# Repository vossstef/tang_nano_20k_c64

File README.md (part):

# C64Nano

The C64Nano is a port of some [MiST](https://github.com/mist-devel/mist-board/wiki) and
[MiSTer](https://mister-devel.github.io/MkDocs_MiSTer/) core components for the
[C64](https://en.wikipedia.org/wiki/Commodore_64):

| Board      | FPGA       | support |Note|
| ---        |        -   | -     |-|
| [Tang Nano 20k](https://wiki.sipeed.com/nano20k)     | [GW2AR](https://www.gowinsemi.com/en/product/detail/38/)  | HDMI / LCD |Dualshock via MiSTeryShield20k spare header **or** Joy to DIP |
| [Tang Primer 25K](https://wiki.sipeed.com/hardware/en/tang/tang-primer-25k/primer-25k.html) | [GW5A-25](https://www.gowinsemi.com/en/product/detail/60/) | HDMI |no Dualshock, no Retro D9 Joystick, no MIDI |
| [Tang Mega 60k NEO](https://wiki.sipeed.com/hardware/en/tang/tang-mega-60k/mega-60k.html) | [GW5AT-60](https://www.gowinsemi.com/en/product/detail/60/) | HDMI / LCD | twin Dualshock |
| [Tang Mega 138k Pro](https://wiki.sipeed.com/hardware/en/tang/tang-mega-138k/mega-138k-pro.html)|[GW5AST-138](https://www.gowinsemi.com/en/product/detail/60/) | HDMI / LCD |twin Dualshock |
| [Tang Console 60K NEO](https://wiki.sipeed.com/hardware/en/tang/tang-console/mega-console.html)|[GW5AT-60](https://www.gowinsemi.com/en/product/detail/60/) | HDMI / LCD |twin Dualshock, no Retro D9 Joystick|

Be aware that the [VIC20](https://en.wikipedia.org/wiki/VIC-20) ([VIC20Nano](https://github.com/vossstef/VIC20Nano)),
[Atari 2600 VCS](https://en.wikipedia.org/wiki/Atari_2600) ([A2600Nano](https://github.com/vossstef/A2600Nano)), [Apple IIe](https://en.wikipedia.org/wiki/Apple_IIe) ([NanoApple2](https://github.com/vossstef/NanoApple2)) had been ported too in similar manner.  

This project relies on an external µC being connected to the Tang Nano 20K. You can use a [M0S Dock BL616](https://wiki.sipeed.com/hardware/en/maixzero/m0s/m0s.html), [Raspberry Pi Pico (W)](https://www.raspberrypi.com/documentation/microcontrollers/pico-series.html) or [esp32-s2](https://www.espressif.com/en/products/socs/esp32-s2)/[s3](https://www.espressif.com/en/products/socs/esp32-s3) and use the [FPGA companion firmware](http://github.com/harbaum/FPGA-Companion). Basically a µC acts as USB host for USB devices and as an OSD controller using a [SPI communication protocol](https://github.com/harbaum/MiSTeryNano/blob/main/SPI.md).

Onboard BL616 µC  
* If you don't need the WIFI modem on a TN20K then even the onboard BL616 µC (normally used for bitstream programming) can be used. A dedicated FPGA bitstream and FPGA companion firmware is needed in that configuration. The onboard BL616 µC is presently supported for TN20K and Console 60K boards. WIFI modem is supported on Console 60K too. There is an extern powered (see ->) [USB Hub](https://github.com/harbaum/FPGA-Companion/blob/main/console_usbhub_and_power_over_usb-a.png) + USB-A to USB-A cable + USB-A Power Supply Plug needed to supply the board and at the same time provide USB ports for USB Keyboard and e.g. USB Joystick or Mouse.

For the [M0S Dock](https://wiki.sipeed.com/hardware/en/maixzero/m0s/m0s.html) BL616 [µC](https://en.bouffalolab.com) there is a:

* [Optional custom carrier board MiSTeryShield20k](https://github.com/harbaum/MiSTeryNano/tree/main/board/misteryshield20k/README.md)
* [M0S PMOD Adapter](https://github.com/harbaum/MiSTeryNano/blob/main/board/m0s_pmod) for Primer / Mega / Console Boards
* [Optional case](https://github.com/harbaum/MiSTeryNano/blob/main/board/misteryshield20k/housing3D)
* [Dualshock Adapter / Cable](/board/misteryshield20k_ds2_adapter/misteryshield20k_ds2_adapter_cable.md)

and for the Raspberry PiPico (RP2040 µC) there is a:

* [Optional custom carrier board MiSTeryShield20k Raspberry PiPico](/board/misteryshield20k_rpipico/README.md)
* [Dualshock Adapter / Cable](/board/misteryshield20k_ds2_adapter/misteryshield20k_ds2_adapter_cable.md)
* [Optional custom PMOD RP2040-Zero](/board/pizero_pmod/README.md) for Primer / Mega / Console Boards
* [Optional custom PMOD PiPico W](/board/pipico_pmod/README.md) incl. WIFI-modem for Primer / Mega / Console Boards
  
Original C64 core by Peter Wendrich and c1541 by [darfpga](https://github.com/darfpga).  
All HID components and µC firmware by Till Harbaum

Features:

* PAL 800x576p@50Hz or NTSC 800x480p@60Hz HDMI Video and Audio Output
* TFT-LCD module 800x600 [SH500Q01Z](https://dl.sipeed.com/Accessories/LCD/500Q01Z-00%20spec.pdf) + Speaker support
* USB Keyboard
* [USB Joystick](https://en.wikipedia.org/wiki/Joystick) or [USB Gamepad](https://en.wikipedia.org/wiki/Gamepad)
* [USB Mouse](https://en.wikipedia.org/wiki/Computer_mouse) as [c1351](https://en.wikipedia.org/wiki/Commodore_1351) Mouse emulation
* [USB Gamepad](https://en.wikipedia.org/wiki/Gamepad) Stick as [Paddle](https://www.c64-wiki.com/wiki/Paddle) Emulation
* [USB XBOX 360 Controller](https://en.wikipedia.org/wiki/Xbox_360_controller) as Joystick or Paddle
* [legacy D9 Joystick](https://en.wikipedia.org/wiki/Atari_CX40_joystick) (Atari / Commodore digital type)
* Joystick emulation on Keyboard Numpad
* [Dualshock 2 Controller Gamepad](https://en.wikipedia.org/wiki/DualShock) for [MiSTeryShield20k](https://github.com/harbaum/MiSTeryNano/tree/main/board/misteryshield20k/README.md) via spare [pinheader](/board/misteryshield20k_ds2_adapter/misteryshield20k_ds2_adapter_cable.md). Adapter [venice1200](https://github.com/venice1200)
* [Dualshock 2 Gamepad](https://en.wikipedia.org/wiki/DualShock) DPad / left Stick as Joystick
* [Dualshock 2 Gamepad](https://en.wikipedia.org/wiki/DualShock) Sticks as [Paddle](https://www.c64-wiki.com/wiki/Paddle) Emulation (analog mode)
* Emulation of [C64GS Cheetah Annihilator](https://en.wikipedia.org/wiki/Commodore_64_Games_System) Joystick 2nd Trigger Button (Pot X/Y)
* emulated [1541 Diskdrive](https://en.wikipedia.org/wiki/Commodore_1541) on FAT/extFAT microSD card with parallel bus [Speedloader Dolphin DOS 2](https://rr.pokefinder.org/wiki/Dolphin_DOS). [GER manual](https://www.c64-wiki.de/wiki/Dolphin_DOS)
* c1541 DOS ROM selection
* Cartridge ROM (*.CRT) loader
* Direct BASIC program (*.PRG) injection loader
* Tape (*.TAP) image loader as [C1530 Datasette](https://en.wikipedia.org/wiki/Commodore_Datasette)
* Loadable 8K Kernal ROM (*.BIN)
* [VIC-II](https://en.wikipedia.org/wiki/MOS_Technology_VIC-II) revision and [6526](https://en.wikipedia.org/wiki/MOS_Technology_CIA) / 8521 selection
* [SID](https://en.wikipedia.org/wiki/MOS_Technology_6581) revision 6581 or 8580 selectable
* 2nd dual SID Option and loadable Filter curves
* emulated [RAM Expansion Unit (REU)](https://en.wikipedia.org/wiki/Commodore_REU) or [GeoRAM](https://en.wikipedia.org/wiki/GeoRAM)
* On Screen Display (OSD) for configuration and loadable image selection (D64/G64/CRT/PRG/BIN/TAP/FLT)
* Physical MIDI-IN and OUT
* RS232 Serial Interface [VIC-1011](http://www.zimmers.net/cbmpics/xother.html) or [UP9600](https://www.pagetable.com/?p=1656) mode to Tang onboard USB-C serial port or external hw pin.
* Swiftlink-232 [6551](https://en.wikipedia.org/wiki/MOS_Technology_6551) WIFI Modem Interface to FPGA-Companion up to 38400 Baud
* Freezer support (e.g. Action Replay)

## Installation

The installation of C64 Nano on the Tang Nano 20k board can be done using a Linux PC or a Windows PC
[(Instruction)](INSTALLATION_WINDOWS.md).

## c64 Nano on Tang Primer 25K

See [Tang Primer 25K](TANG_PRIMER_25K.md). PMOD TF-CARD V2 is required !

## c64 Nano on Tang Mega 60k NEO

See [Tang Mega 60K NEO](TANG_MEGA_60K.md)

## c64 Nano on Tang Mega 138k Pro

See [Tang Mega 138K Pro](TANG_MEGA_138Kpro.md)

## c64 Nano on Tang Console 60k NEO

See [Tang Console 60K NEO](TANG_CONSOLE_60K.md)

## c64 Nano with LCD and Speaker

See [Tang Nano LCD](TANG_NANO_20k_LCD.md)

## emulated Diskdrive c1541

Emulated 1541 on a regular FAT/exFAT formatted microSD card including parallel bus Speedloader Dolphin DOS 2.0.
Copy a D64 Disk image to your sdcard and rename it to **disk8.d64** as default boot image.
Add further D64 or G64 images as you like and insert card in TN slot. LED 0 acts as Drive activity indicator.

> [!TIP]
> Disk directory listing: [(or F7 keypress)](https://project64.c64.org/hw/dolphindos.txt)  
> command:  
> LOAD"$",8  
> LIST  
> Load first program from Disk: (or just LOAD if Dolphin Kernal active)  
> LOAD"*",8  
> RUN  

c1541 DOS ROM can be selected from OSD (default Dolphin DOS 2.0, CBM DOS, SpeedDos Plus or JiffyDOS)
In case a program don't load correctly select via OSD the factory default CBM DOS an give it a try.

## Cartridge ROM Loader (.CRT)

Cartridge ROM can be loaded via OSD file selection.
Copy a *.CRT to your sdcard and rename it to **c64crt.crt** as default boot cartridge ROM.
Prevent the cartridge load at boot by OSD CRT selection **No Disk** , **Save settings** and System **Cold Boot**.
> [!TIP]
> **Detach Cartridge** by OSD:
> ```temporary``` **Cartridge unload & Reset** ```permanent``` **No Disk**, **Save settings** and System **Cold Boot**

> [!IMPORTANT]
> Be aware that some Freezer Card CRT might require to use the standard C64 Kernal and the standard C1541 CBM DOS.

## BASIC Program Loader (.PRG)

A BASIC Program *.PRG file can be loaded via OSD file selection.
Copy a .PRG to your sdcard and rename it to **c64prg.prg** as default boot basic program. Prevent the PRG load at boot by OSD PRG selection **No Disk** , **Save settings** and **Reset** or System **Cold Boot**.
> [!TIP]
> Check loaded file by command: **LIST**

> [!IMPORTANT]
> command: **RUN**

## Tape Image Loader (*.TAP)

A [Tape](https://en.wikipedia.org/wiki/Commodore_Datasette) *.TAP file can be loaded via OSD file selection
In order to start a tape download choose C64 CBM Kernal (mandatory as Dolphin DOS doesn't support Tape). Best to save Kernal OSD selection via **Save settings**.
> [!IMPORTANT]
> command: **LOAD**  
> ___ Only if you have [Exbasic Level II](https://www.c64-wiki.de/index.php?title=Exbasic_Level_II&oldid=261004). CRT Basic loaded then use command: 
> **LOAD***  
> Screen will blank!

The file is loaded automatically as soon as TAP file selected via OSD (no need to press PLAY TAPE button) in case ***no** TAP had been previously selected*.
As mentioned screen will blank for several seconds and then display briefly the filename of the to be loaded file. It will blank shortly afterwards again till load completed and take a lot of time...
Copy a *.TAP to your sdcard and rename it to **c64tap.tap** as default tape mountpoint.
For **Tape unload** use OSD TAP selection **No Disk** and **Reset** or System **Cold Boot**
> [!WARNING]
> After board power-up or coldboot a TAP file will **not autoloaded** even if TAP file selection had been saved or c64tap.tap mountpoint available !
> Unblock loader by OSD TAP selection **No Disk** or simply select again the desired TAP file to be loaded after you typed **LOAD**

> [!TIP]
> Check loaded file by command: **LIST**

> [!IMPORTANT]
> command: **RUN**

> [!NOTE]
> The available (muffled) Tape Sound audio can be disabled from OSD.

## Kernal Loader (.BIN)

The build-in Dolphin Kernal is the power-up default C64 Kernal with an excellent C1541 speedloader.
> [!TIP]
> If you are fine with that then there is no need to load another Kernal via OSD and just select OSD Kernal BIN selection **No Disk** and **Save settings**!

In general Kernal ROM files *.BIN can be loaded via OSD selection.
Copy a 8K C64 Kernal ROM .BIN to your sdcard and rename it to **c64kernal.bin** as default boot Kernal.
Prevent Kernal load by OSD Kernal BIN selection **No Disk** and **Save settings** and do a **power-cyle** of the board. In this case the build-in Dolphin Kernal will by default be used after next power cycle.

## SID Filter Curve (.FLT)

Custom Filters curves can optionally be loaded via OSD.
> [!TIP]https://www.telnetbbsguide.com/bbs/software/image-bbs/
> This is in most cases not needed and build-in filters curves are already an optimum.

> [!NOTE]
> Remember to select the 6581 chip, not the 8580.
> Select 'Custom 1' as the filter to activate it. When a custom filter is loaded, there's no difference between custom options Custom 1, 2, and 3. Selecting 'Default' switches back to the built-in filter curve.
https://www.telnetbbsguide.com/bbs/software/image-bbs/
Prevent Filter curve load by OSD Kernal **FLT** selection **No Disk** and **Save settings** and **power-cyle** of the board.

## Core Loader Sequencing

The core will after power cycle/ cold-boot start downloading the images on the sdcard in the following order:

> [!NOTE]
> (1) BIN Kernal, (2) CRT ROM, (3) PRG Basic and finally (4) FLT.

## emulated RAM Expansion Unit REU 1750

For those programs the require a [RAM Expansion Unit (REU)](https://en.wikipedia.org/wiki/Commodore_REU) it can be activated by OSD on demand.

Playing [Sonic the Hedgehog V1.2](https://csdb.dk/release/?id=212523)
Enable REU, and load the PRG.  
Playing around with [GEOS](https://en.wikipedia.org/wiki/GEOS_(8-bit_operating_system))
Enable REU, select c1541 CBM DOS ROM and load the PRG.

## Push Button / DIP Switch utilization

* S1 swap the Joystick Ports if OSD **Swap Joys** is set to Off mode.

* S2 open OSD

> [!CAUTION]
> A FLASH programm attempt without keeping the board in reset may lead to corruption of the C1541 DOS images stored in FLASH requiring re-programming.
> Nano 20k S2 keep pressed during power-up for FLASH programming of FPGA bitstream  

## OSD

invoke by F12 keypress

* Reset
* Cold Reset + memory scrubbing
* Audio Volume + / -
* Scanlines effect %
* Widescreen activation
* HID device selection for Joystick Port 1 and Port 2
* REU activation
* c1541 Drive disk image selection
* c1541 Disk write protetcion
* c1541 Reset
* c1541 DOS ROM selection
* MIDI configuration
* PAL / NTSC Video mode
* VIC-II revision, 6526 / 8521 and SID 6561/8580 selection
* SID Filter selection
* geoRAM activation
* Loader (CRT/PRG/BIN/TAP/FLT) file selection
* Joystick Port Swap
* Cartridge unload

## Gamecontrol support

<u>legacy single D9 Digital Joystick.</u>  
OSD: **Retro D9**
Atari ST type of Joystick 2nd button supported using a MiSTeryNano shield.  
Don't configure e.g. [ArcadeR](https://retroradionics.com) for C64 mode rather than normal digital 2nd button mode (2nd trigger button connect signal to ground)

<u>USB Joystick(s)</u>.  
OSD: **USB #1 Joy** or **USB #2 Joy**
Also [RII Mini Keyboard i8](http://www.riitek.com/product/220.html) left Multimedia Keys are active if **USB #1 Joy** selected.

<u>Dualshock 2 Gamepad Stick or Dpad as Joystick.</u>.  
OSD: **DS #1 Joy** or **DS #2 Joy**
At the moment Dpad only for original Pad. Some clone devices support at the same time Dpad and left stick simultaniously. ```circle and cross``` Buttons as Trigger:

> [!IMPORTANT]
> In a [MiSTeryShield20k](https://github.com/harbaum/MiSTeryNano/tree/main/board/misteryshield20k) configuration Dualshock is supported via the internal ``spare J8`` pinheader.
> See [MiSTeryShield20k DS2 Adapter / Cable](/board/misteryshield20k_ds2_adapter/misteryshield20k_ds2_adapter_cable.md) for further information. Thx [venice1200](https://github.com/venice1200) !

> [!NOTE]
> TN20k: You have to select OSD **DS2 #2 Joy** or **DS #2 Paddle** for a ``MiSTeryShield20k`` configuration.
> TN20k: You have to select OSD **DS2 #1 Joy** or **DS #1 Paddle** if you use the ``Sipeed Joy to DIP`` adapter.
> Single DS interface active at the same time!

<u>Keyboard Numpad.</u>  
OSD: **Numpad**

|Numpad| |Numpad|
|-|-|-|
|0  Trigger|8  Up|.  Trigger 2|
|4  Left|-|6  Right|
|-|2  Down|-|

<u>Mouse.</u>  
OSD: **Mouse**
USB Mouse as c1351 Mouse emulation.

<u>Dualshock 2 Gamepad</u> as Paddle  
OSD: **DS #1 Paddle** or **DS #2 Paddle**
Dualshock left Stick in analog mode as VC-1312 Paddle emulation.
ANALOG Paddle mode will be indicated by DS 2 red light indicator.
> [!NOTE]
> TN20k:
> single Dualshock support only
> 4 Paddles mapped to a single Gamepad (X/Y) and both Sticks.
> **square** , **cross**, **circle** and **triangle** used as 4 Trigger buttons
> ``Joyport 1:``  **DS2 #1 Paddle**
> ``Joyport 2:``  **DS2 #1 Paddle**
> or<br>
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
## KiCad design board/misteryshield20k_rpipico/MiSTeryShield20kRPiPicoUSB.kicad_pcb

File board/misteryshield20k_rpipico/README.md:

# MiSTeryShield20k RPiPico USB board

Features:

* Headers to plug the Tang Nano 20K
* Headers to plug the [Raspberry Pi Pico (W)](https://www.raspberrypi.com/products/raspberry-pi-pico)
* Atari / Commodore style joystick interface
  * Supports up to two buttons
  * Including 5V supply and 5V level shifters
  * Works with DB9 joystcks and mice
  * MIDI
    * MIDI OUT with driver chip to protect Tang Nano 20K
    * MIDI IN with optocoupler to protect Tang Nano 20K
* 4 x USB-A Interface
* Spare header for FPGA IO / [Dualshock 2 Adapter cable](/board/misteryshield20k_ds2_adapter/misteryshield20k_ds2_adapter_cable.md) (**no DS2 connector onboard**)
* Debug header for Pico UART and e.g. FPGA UART
* 3 x PiPico Status LED
* 3D STEP model to ease case development
* [CERN-OHL-S](https://cern-ohl.web.cern.ch/home) license

PCBA production files for [JLCPCB](https://jlcpcb.com) are availble [here](Output/production)  
(Fully assembled boards can orderd based on BOM partlist, excluding the TN20k and PiPico connector)  

The great PCB Layout work using [KiCad](https://www.kicad.org) had been done by [cantclosevi](https://github.com/cantclosevi). Thx Michal !

**Version history**
| Version  | Issue|  Change to earlier version|rework|
|----------|-|--------|-|
|0|engineering sample|DS2 connector rotated|mount DS2 bottom|
|1|DS2 rotation fixed|mechanical positioning|-|
|2|DS2 removed and positioning fixed|MIDI IN pin 4+5 reversed|[Instruction](rework/REWORK_HW2.MD)|
|3| none known |MIDI IN fix|-|

# Pin usage

| Pin  | Signal | Description            |
|------|--------|------------------------|
| GP0  | UART_TX| Serial debug output    |
| GP1  | UART_RX| Serial debug input     |
| GP2  | USB D+ | USB PIO host D+        |
| GP3  | USB D- | USB PIO host D-        |
| GP4  | LED 1  | indicator mice         |
| GP5  | LED 2  | indicator keyboard     |
| GP6  | LED 3  | indicator joystick     |
| GP16 | MISO   | SPI data from FPGA     |
| GP17 | CSn    | SPI chip select to FPGA|
| GP18 | SCK    | SPI clock to FPGA      |
| GP19 | MOSI   | SPI data to FPGA       |
| GP20 |spare   | spare                  |
| GP22 | IRQn   | SPI interrupt from FPGA|

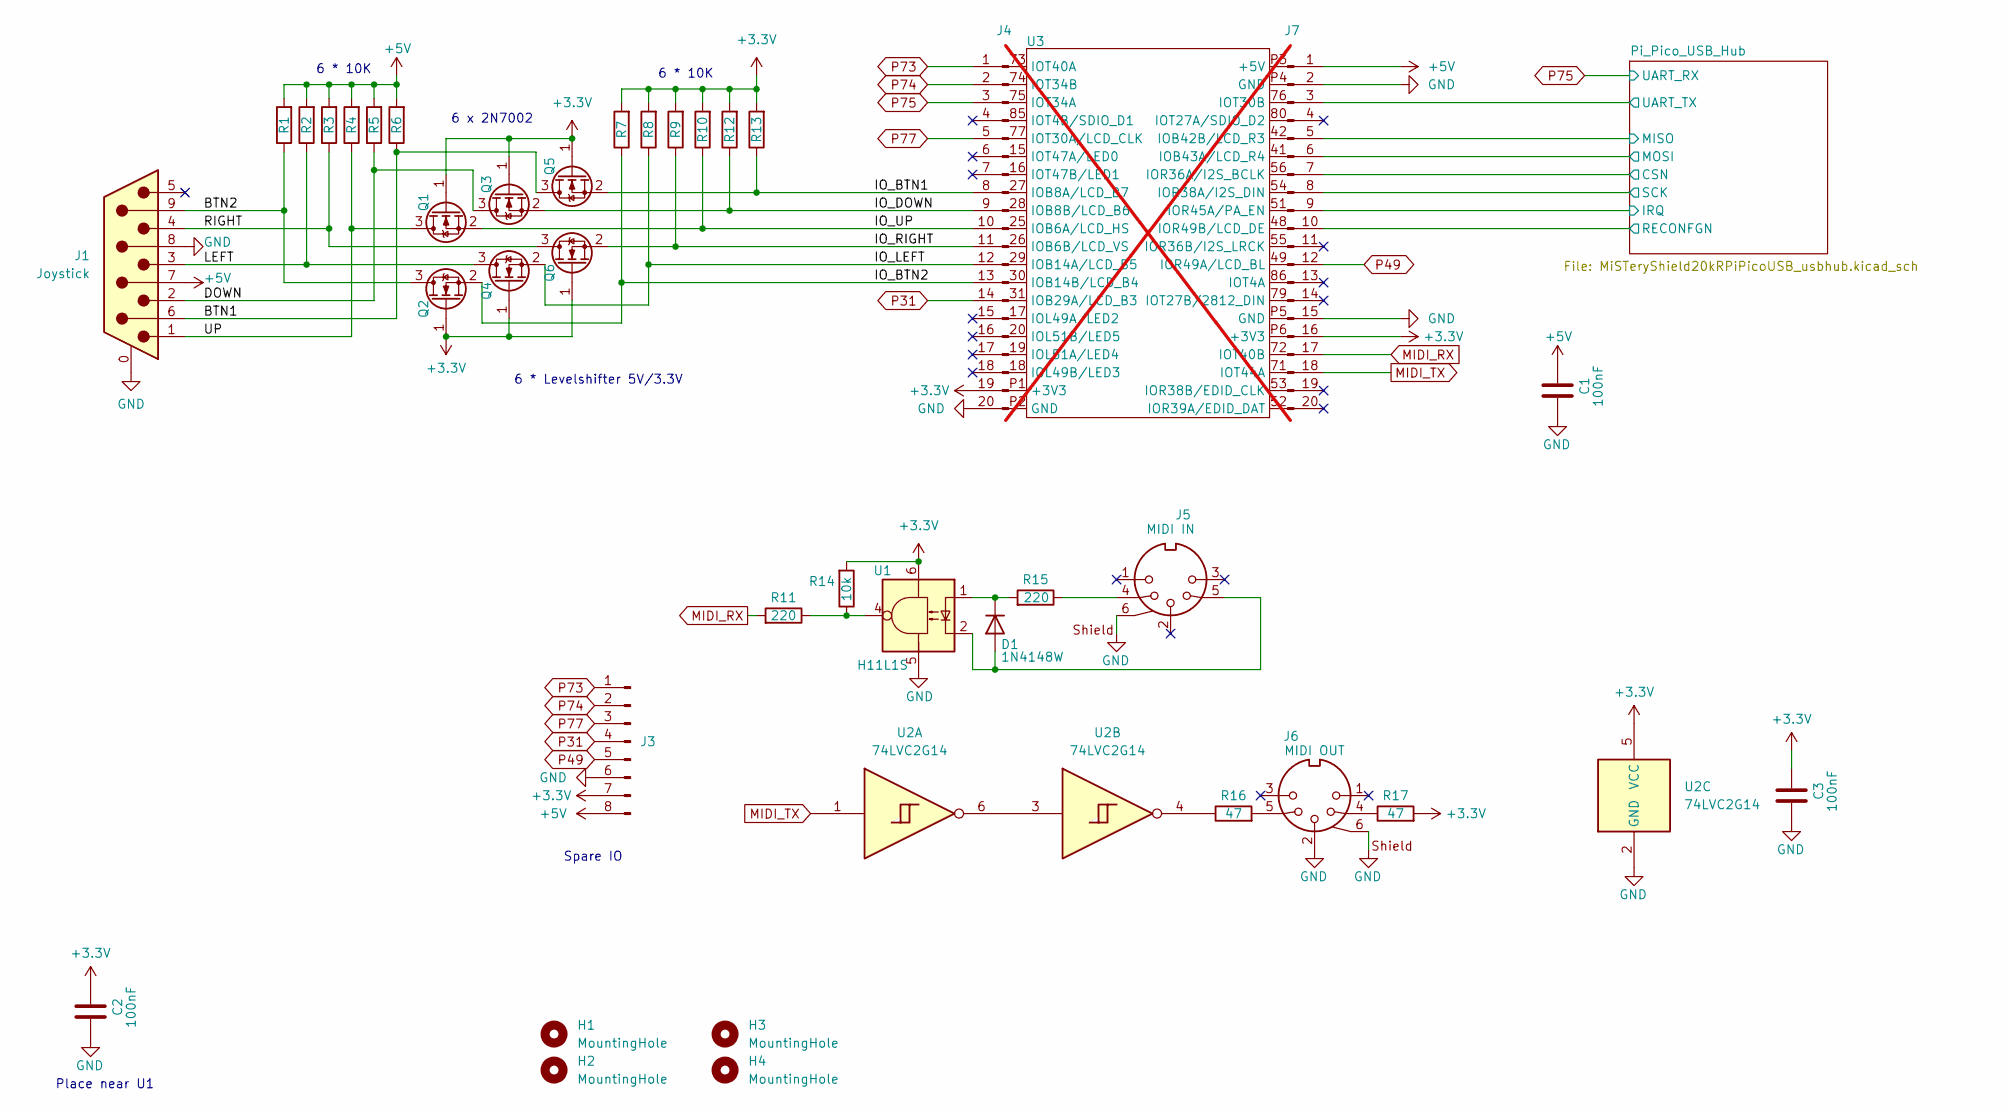
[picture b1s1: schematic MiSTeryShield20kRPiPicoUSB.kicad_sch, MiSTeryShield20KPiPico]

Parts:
C1, C2, C3: 100nF; C_0805_2012Metric; LCSC Part # C49678
D1: 1N4148W; D_SOD-123; LCSC Part # C81598
H1, H2, H3, H4: MountingHole; MountingHole_3.2mm_M3
J1: Joystick; DSUB-9_Male_Horizontal_P2.77x2.84mm_EdgePinOffset7.70mm_Hou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; LCSC Part # C141880
J3: Conn_02x04_Pin; PinHeader_2x04_P2.54mm_Vertical; LCSC Part # C7501275
J4, J7: Conn_01x20_Pin; PinSocket_1x20_P2.54mm_Vertical; LCSC Part # C18078139
J5: MIDI IN; DIN-5_180degree; LCSC Part # C2939346
J6: MIDI OUT; DIN-5_180degree; LCSC Part # C2939346
Q1, Q2, Q3, Q4, Q5, Q6: 2N7002; SOT-23; LCSC Part # C8545
R1, R2, R3, R4, R5, R6, R7, R8, R9, R10, R12, R13, R14: 10k; R_0805_2012Metric; LCSC Part # C17414
R11, R15: 220; R_0805_2012Metric; LCSC Part # C17557
R16, R17: 47; R_0805_2012Metric; LCSC Part # C17714
U1: H11L1S; SMDIP-6_W9.53mm; LCSC Part # C78589
U2: 74LVC2G14; SOT-23-6; LCSC Part # C5375976
U3: TangNano-20K; not fitted

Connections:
+3.3V: C2.2, C3.2, J3.7, J4.19, J7.16, Q1.1 (G), Q2.1 (G), Q3.1 (G), Q4.1 (G), Q5.1 (G), Q6.1 (G), R7.2, R8.2, R9.2, R10.2, R12.2, R13.2, R14.2, R17.2, U1.6, U2.5 (VCC); also elsewhere on the board
+5V: C1.2, J1.7, J3.8, J7.1, R1.2, R2.2, R3.2, R4.2, R5.2, R6.2; also elsewhere on the board
/BTN1: J1.6, Q5.3 (D), R6.1
/BTN2: J1.9, Q2.3 (D), R1.1
/DOWN: J1.2, Q3.3 (D), R5.1
/IO_BTN1: J4.8, Q5.2 (S), R13.1
/IO_BTN2: J4.13, Q2.2 (S), R7.1
/IO_DOWN: J4.9, Q3.2 (S), R12.1
/IO_LEFT: J4.12, Q4.2 (S), R8.1
/IO_RIGHT: J4.11, Q6.2 (S), R9.1
/IO_UP: J4.10, Q1.2 (S), R10.1
/LEFT: J1.3, Q4.3 (D), R2.1
/Pi_Pico_USB_Hub/CSN: J7.7; also elsewhere on the board
/Pi_Pico_USB_Hub/IRQ: J7.9; also elsewhere on the board
/Pi_Pico_USB_Hub/MISO: J7.5; also elsewhere on the board
/Pi_Pico_USB_Hub/MOSI: J7.6; also elsewhere on the board
/Pi_Pico_USB_Hub/RECONFGN: J7.10; also elsewhere on the board
/Pi_Pico_USB_Hub/SCK: J7.8; also elsewhere on the board
/Pi_Pico_USB_Hub/UART_TX: J7.3; also elsewhere on the board
/RIGHT: J1.4, Q6.3 (D), R3.1
/UP: J1.1, Q1.3 (D), R4.1
GND: C1.1, C2.1, C3.1, J1.0 (PAD), J1.8, J3.6, J4.20, J5.6, J6.2, J6.6, J7.2, J7.15, U1.5, U2.2 (GND); also elsewhere on the board
MIDI_RX: J7.17, R11.2
MIDI_TX: J7.18, U2.1
unnamed: D1.2 (A), J5.5, U1.2
unnamed: D1.1 (K), R15.2, U1.1
unnamed: J5.4, R15.1
unnamed: J6.4, R17.1
unnamed: J6.5, R16.2
unnamed: R11.1, R14.1, U1.4
unnamed: R16.1, U2.4
unnamed: U2.3, U2.6
P31: J3.4, J4.14
P49: J3.5, J7.12
P73: J3.1, J4.1
P74: J3.2, J4.2
P75: J4.3; also elsewhere on the board
P77: J3.3, J4.5

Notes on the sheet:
6 * Levelshifter 5V/3.3V
Spare IO
Place near U1
6 * 10K
6 x 2N7002

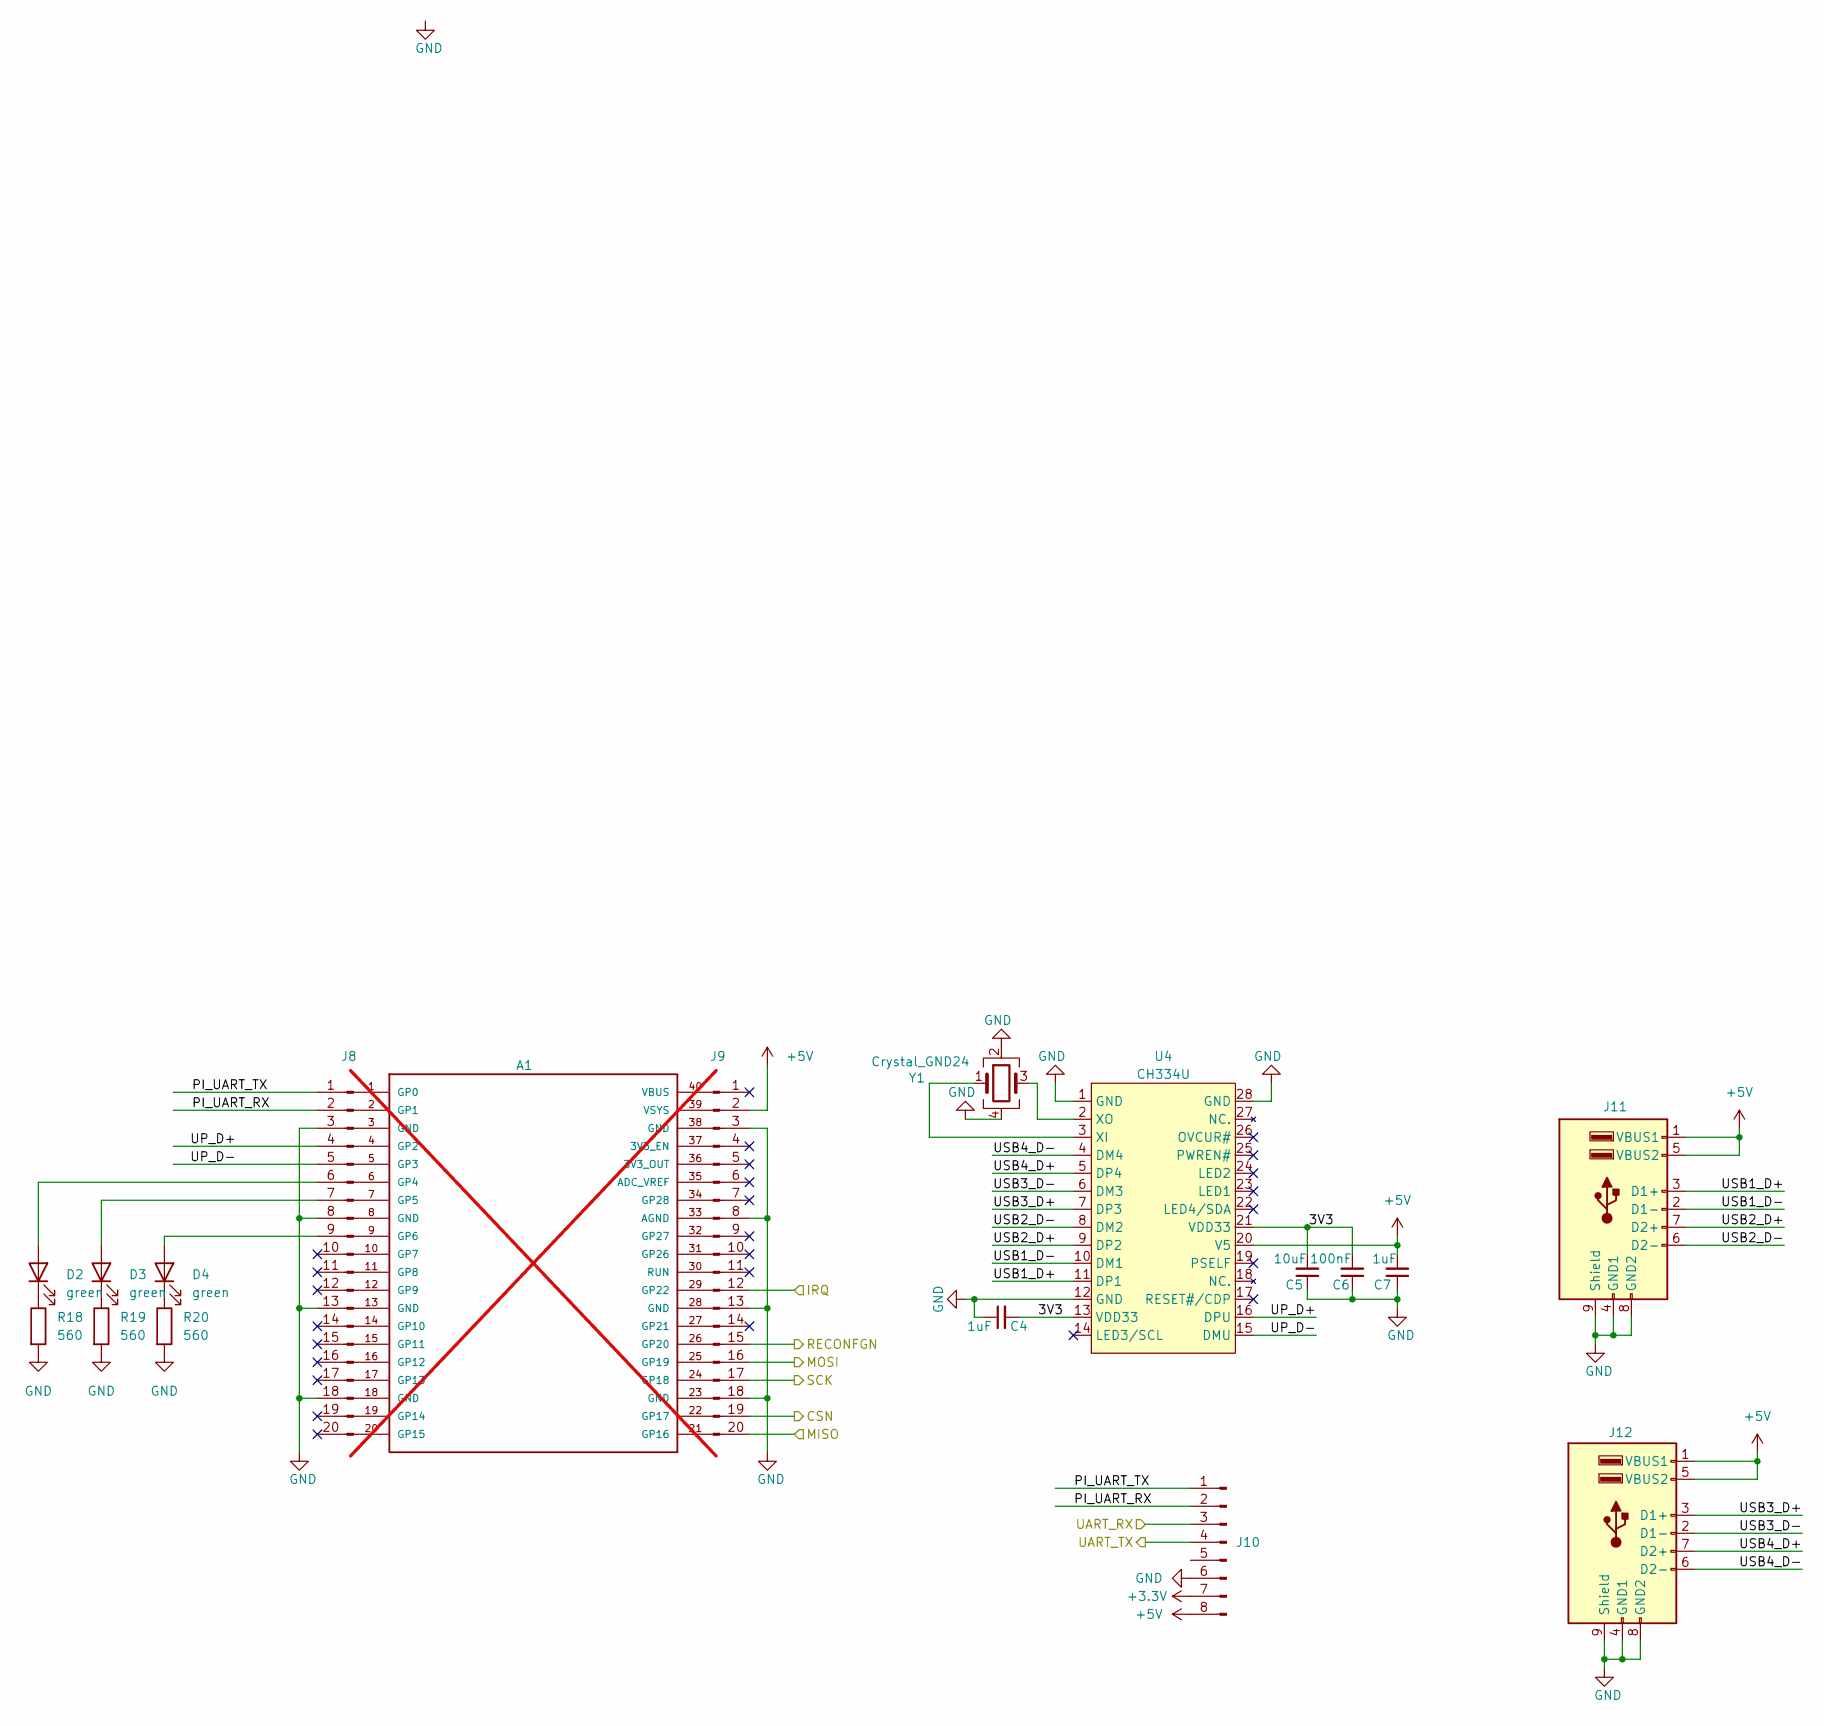
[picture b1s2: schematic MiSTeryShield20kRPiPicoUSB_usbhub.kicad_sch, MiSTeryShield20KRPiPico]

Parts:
A1: Raspberry_Pi_Pico_W; not fitted
C4, C7: 1uF; C_0805_2012Metric; LCSC Part # C28323
C5: 10uF; C_0805_2012Metric; LCSC Part # C15850
C6: 100nF; C_0805_2012Metric; LCSC Part # C49678
D2, D3, D4: green; LED_0805_2012Metric; LCSC Part # C2297
J8, J9: Conn_01x20_Pin; PinSocket_1x20_P2.54mm_Vertical; LCSC Part # C18078139
J10: Conn_02x04_Pin; PinHeader_2x04_P2.54mm_Vertical; LCSC Part # C7501275
J11, J12: USB_A_Stacked; USB_A_Wuerth_61400826021_Horizontal_Stacked; LCSC Part # C456021
R18, R19, R20: 560; R_0805_2012Metric; LCSC Part # C28636
U4: CH334U; SSOP-28_3.9x9.9mm_P0.635mm; LCSC Part # C5187524
Y1: Crystal_GND24; Crystal_SMD_3225-4Pin_3.2x2.5mm; LCSC Part # C9002

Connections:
+3.3V: J10.7; also elsewhere on the board
+5V: C7.2, J9.2, J10.8, J11.1 (VBUS1), J11.5 (VBUS2), J12.1 (VBUS1), J12.5 (VBUS2), U4.20 (V5); also elsewhere on the board
/Pi_Pico_USB_Hub/3V3: C4.2, C5.2, C6.2, U4.13 (VDD33), U4.21 (VDD33)
/Pi_Pico_USB_Hub/CSN: J9.19; also elsewhere on the board
/Pi_Pico_USB_Hub/IRQ: J9.12; also elsewhere on the board
/Pi_Pico_USB_Hub/MISO: J9.20; also elsewhere on the board
/Pi_Pico_USB_Hub/MOSI: J9.16; also elsewhere on the board
/Pi_Pico_USB_Hub/PI_UART_RX: J8.2, J10.2
/Pi_Pico_USB_Hub/PI_UART_TX: J8.1, J10.1
/Pi_Pico_USB_Hub/RECONFGN: J9.15; also elsewhere on the board
/Pi_Pico_USB_Hub/SCK: J9.17; also elsewhere on the board
/Pi_Pico_USB_Hub/UART_TX: J10.4; also elsewhere on the board
/Pi_Pico_USB_Hub/UP_D+: J8.4, U4.16 (DPU)
/Pi_Pico_USB_Hub/UP_D-: J8.5, U4.15 (DMU)
/Pi_Pico_USB_Hub/USB1_D+: J11.3 (D1+), U4.11 (DP1)
/Pi_Pico_USB_Hub/USB1_D-: J11.2 (D1-), U4.10 (DM1)
/Pi_Pico_USB_Hub/USB2_D+: J11.7 (D2+), U4.9 (DP2)
/Pi_Pico_USB_Hub/USB2_D-: J11.6 (D2-), U4.8 (DM2)
/Pi_Pico_USB_Hub/USB3_D+: J12.3 (D1+), U4.7 (DP3)
/Pi_Pico_USB_Hub/USB3_D-: J12.2 (D1-), U4.6 (DM3)
/Pi_Pico_USB_Hub/USB4_D+: J12.7 (D2+), U4.5 (DP4)
/Pi_Pico_USB_Hub/USB4_D-: J12.6 (D2-), U4.4 (DM4)
GND: C4.1, C5.1, C6.1, C7.1, J8.3, J8.8, J8.13, J8.18, J9.3, J9.8, J9.13, J9.18, J10.6, J11.4 (GND1), J11.8 (GND2), J11.9 (Shield), J12.4 (GND1), J12.8 (GND2), J12.9 (Shield), R18.2, R19.2, R20.2, U4.1 (GND), U4.12 (GND), U4.28 (GND), Y1.2, Y1.4; also elsewhere on the board
unnamed: D2.2 (A), J8.6
unnamed: D2.1 (K), R18.1
unnamed: D3.2 (A), J8.7
unnamed: D3.1 (K), R19.1
unnamed: D4.2 (A), J8.9
unnamed: D4.1 (K), R20.1
unnamed: U4.3 (XI), Y1.1
unnamed: U4.2 (XO), Y1.3
P75: J10.3; also elsewhere on the board

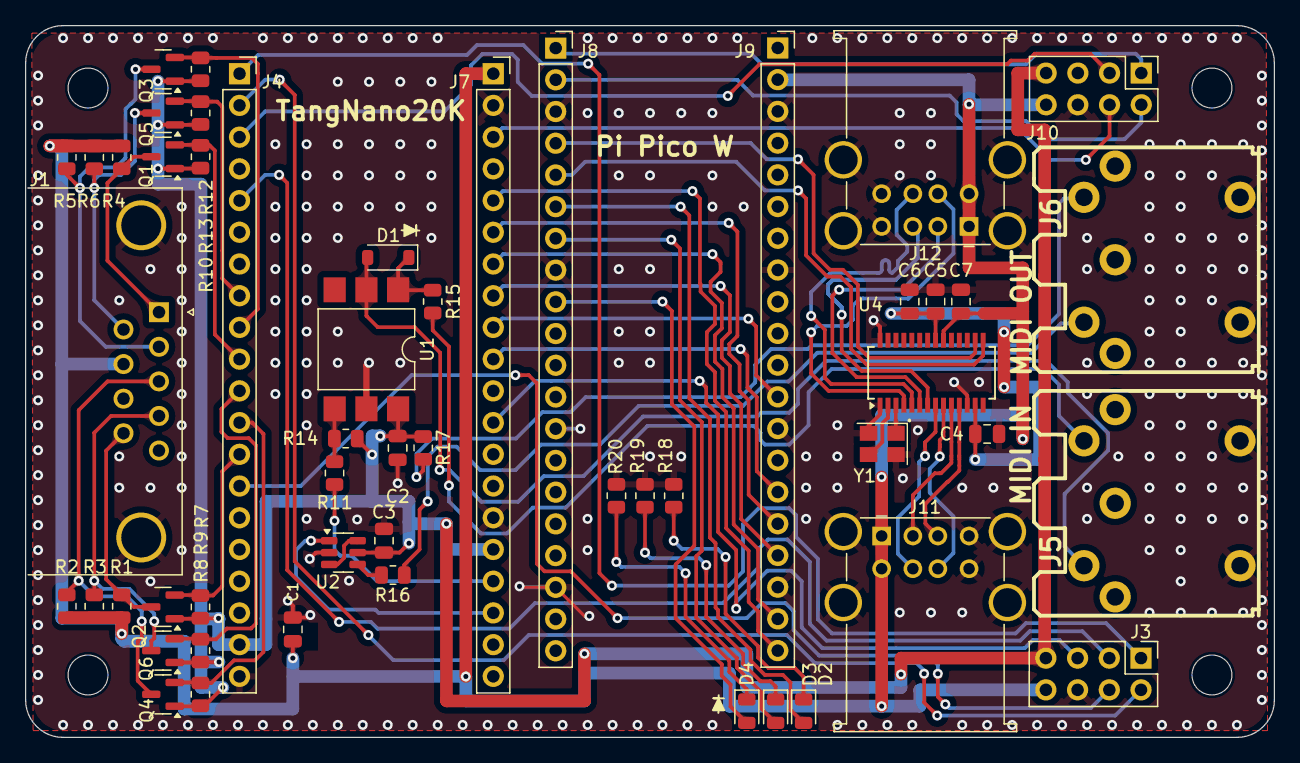
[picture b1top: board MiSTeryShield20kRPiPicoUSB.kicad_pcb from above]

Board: 2 copper layers, 100.0 x 57.0 mm, 56 parts (0 on the bottom side), 59 nets.

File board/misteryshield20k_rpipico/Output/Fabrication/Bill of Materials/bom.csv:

"Reference","Value","Comment","LCSC Part #","Qty"
"C1,C2,C3,C6","100nF","0805","C49678","4"
"C4,C7","1uF","0805","C91185","2"
"C5","10uF","0805","C1952580","1"
"D1","1N4148W","SOD-123","C81598","1"
"D2,D3,D4","green","0805","C2297","3"
"J1","Joystick","DSUB-9 Male","C141880","1"
"J3,J10","Conn_02x04_Pin","2x04, P2.54mm","C7501275","2"
"J4,J7,J8,J9","Conn_01x20_Pin","1x20, P2.54mm","C18078139","4"
"J5","MIDI IN","DIN-5_180degree","C2939346","1"
"J6","MIDI OUT","DIN-5_180degree","C2939346","1"
"J11,J12","USB_A_Stacked","","C456021","2"
"Q1,Q2,Q3,Q4,Q5,Q6","BSS123","SOT-23","C79015","6"
"R1,R2,R3,R4,R5,R6,R7,R8,R9,R10,R12,R13,R14","10k","0805","C17414","13"
"R11,R15","220","0805","C17557","2"
"R16,R17","47","0805","C17714","2"
"R18,R19,R20","560","0805","C28636","3"
"U1","H11L1S","SMDIP-6","C78589","1"
"U2","74LVC2G14","SOT-23-6","C5375976","1"
"U4","CH334U","SSOP-28","C5187524","1"
"Y1","Crystal_GND24","SMD 3225 4-Pin","C9002","1"

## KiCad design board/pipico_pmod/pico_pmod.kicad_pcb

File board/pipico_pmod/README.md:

# PMOD PiPico W

Features:
* PMOD carrier for a [Raspberry Pi Pico W](https://www.raspberrypi.com/documentation/microcontrollers/pico-series.html)
* USB-C to e.g. USB-C HUB or HID
* Debug header for Pico UART
* PMOD spare signals on Testpoints
* Status LED's
* [CERN-OHL-S](https://cern-ohl.web.cern.ch/home) license

PCBA production files for [JLCPCB](https://jlcpcb.com) are availble [here](production).  
(Fully assembled boards can orderd based on BOM partlist, excluding the RP2040)  

> [!IMPORTANT]
> Pin headers are already assembled  
> Take the RP2040 variant without pin headers !

| Pin | Signal | Description |
|---|---|---|
| GP0  | UART_TX  | Serial debug output |
| GP1  | UART_RX  | Serial debug input |
| GP2  | USB D+ | USB PIO host D+ |
| GP3  | USB D- | USB PIO host D- |
| GP4  | LED 1 | indicator mouse |
| GP5  | LED 2 | indicator keyboard |
| GP6  | LED 3 | indicator joystick |
| GP16 | MISO | SPI data from FPGA |
| GP17 | CSn | SPI chip select to FPGA |
| GP18 | SCK | SPI clock to FPGA |
| GP19 | MOSI | SPI data to FPGA |
| GP22 | IRQn | SPI interrupt from FPGA |

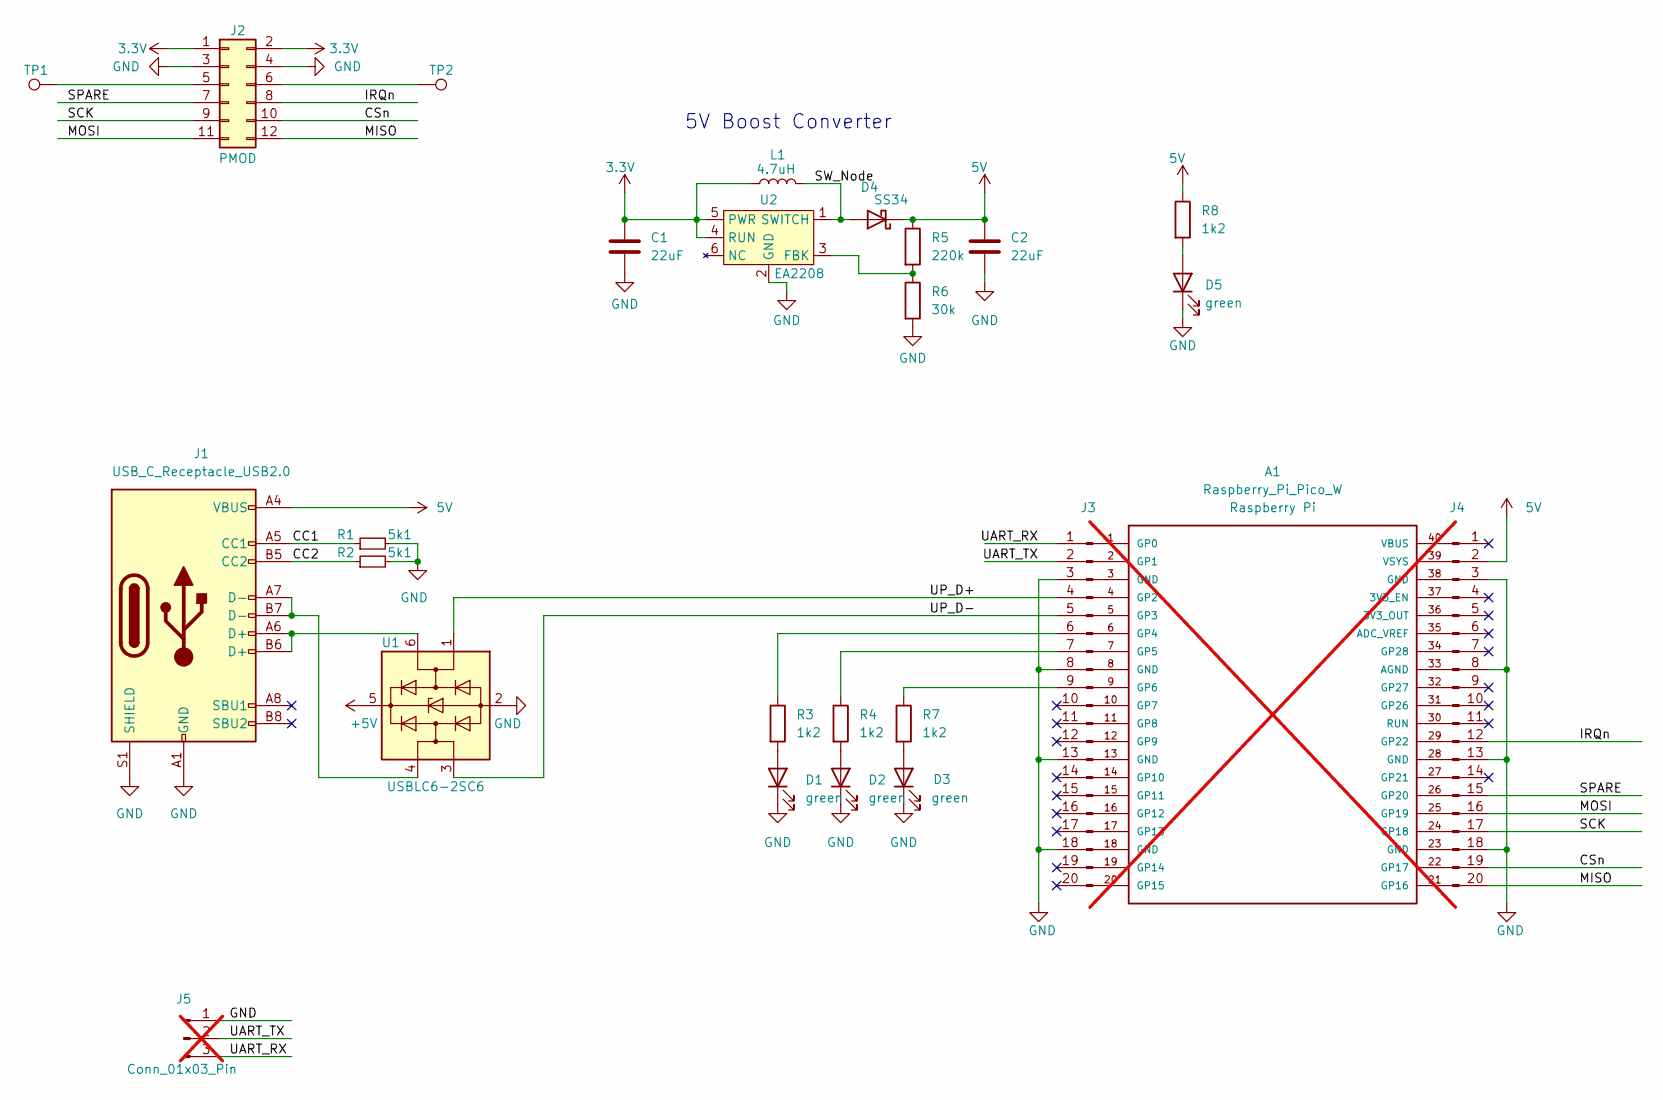
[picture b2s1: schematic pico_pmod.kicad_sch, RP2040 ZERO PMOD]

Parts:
A1: Raspberry_Pi_Pico_W; not fitted
C1, C2: 22uF; C_1206_3216Metric; LCSC Part # C12891
D1, D2, D3, D5: green; LED_0805_2012Metric; LCSC Part # C2297
D4: SS34; D_SMA; LCSC Part # C8678
J1: USB_C_Receptacle_USB2.0; USB_C_Receptacle_HRO_TYPE-C-31-M-12; LCSC C165948
J2: PMOD; PinHeader_2x06_P2.54mm_Horizontal; JLCPCB Position Offset -6.35,-1.5
J3, J4: Conn_01x20_Pin; PinSocket_1x20_P2.54mm_Vertical; LCSC Part # C18078139
J5: Conn_01x03_Pin; PinHeader_1x03_P2.54mm_Vertical; LCSC Part # C2932698; not fitted
L1: 4.7uH; L_6.3x6.3_H3; LCSC Part # C142106
R1, R2: 5k1; R_0402_1005Metric; LCSC C25905
R3, R4, R7, R8: 1k2; R_0805_2012Metric; LCSC Part # C17379
R5: 220k; R_0805_2012Metric; LCSC Part # C17556
R6: 30k; R_0805_2012Metric; LCSC Part # C17621
TP1, TP2: TestPoint; TestPoint_Pad_D1.5mm
U1: USBLC6-2SC6; SOT-23-6; LCSC C2827654
U2: EA2208; SOT-23-6; LCSC Part # C22462489

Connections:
3.3V: C1.1, J2.1, J2.2, L1.1, U2.4 (RUN), U2.5 (PWR)
5V: C2.1, D4.1 (K), J1.A4 (VBUS), J1.A9 (VBUS), J1.B4 (VBUS), J1.B9 (VBUS), J4.2, R5.1, R8.1
+5V: U1.5 (VBUS)
/CC1: J1.A5 (CC1), R1.1
/CC2: J1.B5 (CC2), R2.1
/CSn: J2.10, J4.19
/IRQn: J2.8, J4.12
/MISO: J2.12, J4.20
/MOSI: J2.11, J4.16
/SCK: J2.9, J4.17
/SPARE: J2.7, J4.15
/SW_Node: D4.2 (A), L1.2, U2.1 (SWITCH)
/UART_RX: J3.1, J5.3
/UART_TX: J3.2, J5.2
/UP_D+: J3.4, U1.1 (I/O1)
/UP_D-: J3.5, U1.3 (I/O2)
GND: C1.2, C2.2, D1.1 (K), D2.1 (K), D3.1 (K), D5.1 (K), J1.A1 (GND), J1.A12 (GND), J1.B1 (GND), J1.B12 (GND), J1.S1 (SHIELD), J2.3, J2.4, J3.3, J3.8, J3.13, J3.18, J4.3, J4.8, J4.13, J4.18, J5.1, R1.2, R2.2, R6.2, U1.2 (GND), U2.2 (GND)
unnamed: D1.2 (A), R3.2
unnamed: D2.2 (A), R4.2
unnamed: D3.2 (A), R7.2
unnamed: D5.2 (A), R8.2
unnamed: J1.A6 (D+), J1.B6 (D+), U1.6 (I/O1)
unnamed: J1.A7 (D-), J1.B7 (D-), U1.4 (I/O2)
unnamed: J2.5, TP1.1
unnamed: J2.6, TP2.1
unnamed: J3.6, R3.1
unnamed: J3.7, R4.1
unnamed: J3.9, R7.1
unnamed: R5.2, R6.1, U2.3 (FBK)

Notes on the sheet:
5V Boost Converter

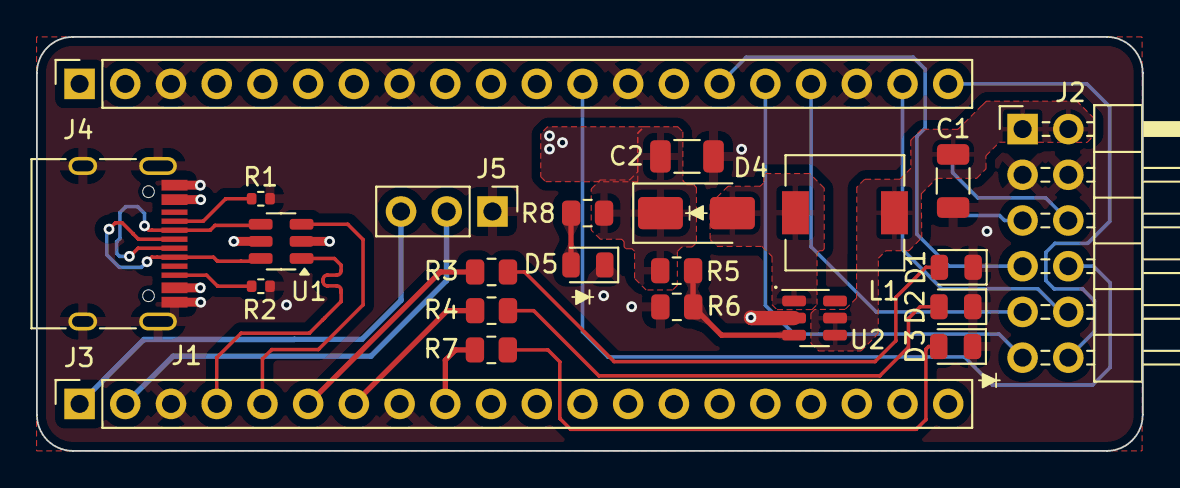
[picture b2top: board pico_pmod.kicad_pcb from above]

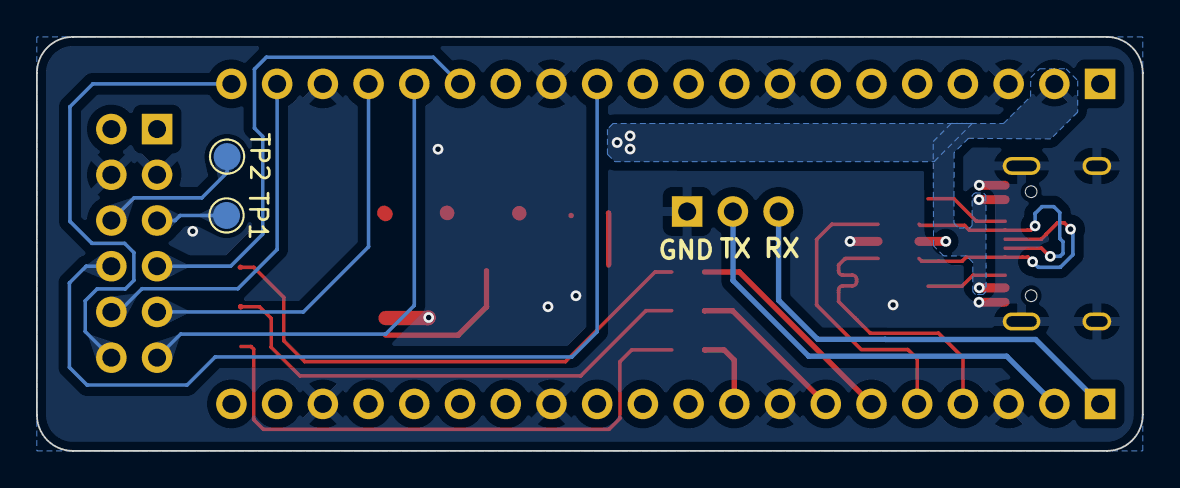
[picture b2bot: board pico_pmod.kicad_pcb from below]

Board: 2 copper layers, 61.4 x 23.0 mm, 25 parts (2 on the bottom side), 28 nets.

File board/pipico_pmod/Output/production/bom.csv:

Designator,Footprint,Quantity,Value,LCSC Part #
"C1, C2",1206,2,22uF,C12891
"D1, D2, D3, D5",0805,4,green,C2297
D4,D_SMA,1,SS34,C8678
J1,USB_C_Receptacle_HRO_TYPE-C-31-M-12,1,USB_C_Receptacle_USB2.0,C165948
J2,PinHeader_2x06_P2.54mm_Horizontal,1,PMOD,C60565
"J3, J4",PinSocket_1x20_P2.54mm_Vertical,2,Conn_01x20_Pin,C18078139
L1,L_6.3x6.3_H3,1,4.7uH,C142106
"R1, R2",0402,2,5k1,C25905
"R3, R4, R7, R8",0805,4,1k2,C17379
R5,0805,1,220k,C17556
R6,0805,1,30k,C17621
U1,SOT-23-6,1,USBLC6-2SC6,C2827654
U2,SOT-23-6,1,EA2208,C22462489

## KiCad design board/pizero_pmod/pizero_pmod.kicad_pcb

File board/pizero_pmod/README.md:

# PMOD PI-Zero

Features:
* PMOD carrier for a [RP2040-ZERO](https://www.waveshare.com/wiki/RP2040-Zero)
* USB-C to a USB-C HUB
* Debug header for Pico UART
* PMOD spare signals on Testpoints
* [CERN-OHL-S](https://cern-ohl.web.cern.ch/home) license

PCBA production files for [JLCPCB](https://jlcpcb.com) are availble [here](production).  
(Fully assembled boards can orderd based on BOM partlist, excluding the RP2040-Zero)  

> [!IMPORTANT]
> Pin headers are already assembled  
> Take the RP2040-Zero variant without pin headers !

| Pin | Signal   | Description |
|-----|----------|---------------------|
| GP0 | UART_TX  | Serial debug output |
| GP1 | UART_RX  | Serial debug input  |
| GP4 | MISO     | SPI data from FPGA  |
| GP5 | CSn      | SPI chip select to FPGA |
| GP6 | SCK      | SPI clock to FPGA   |
| GP7 | MOSI     | SPI data to FPGA    |
| GP8 | IRQn     | SPI interrupt from FPGA |
| GP14| spare    | spare               |

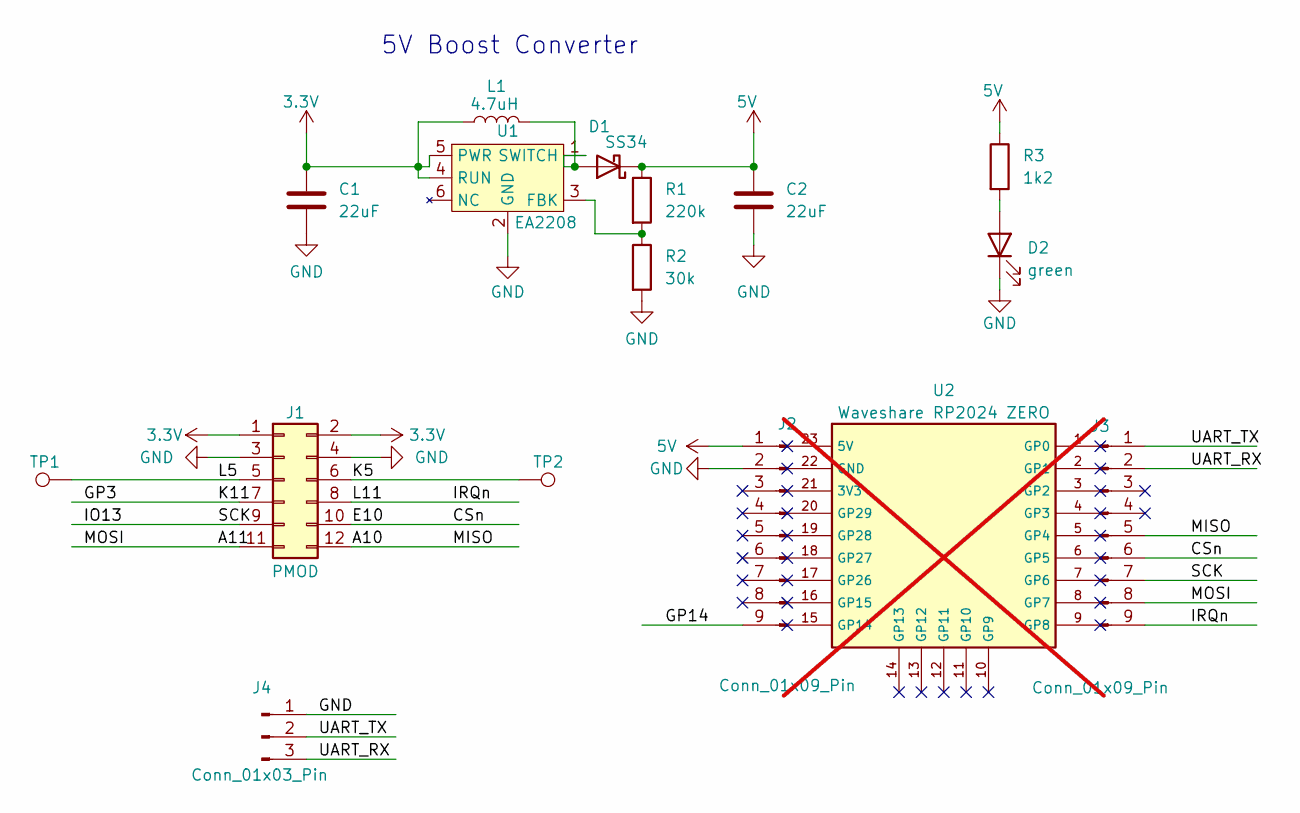
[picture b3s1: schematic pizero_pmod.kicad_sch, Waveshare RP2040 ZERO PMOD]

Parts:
C1, C2: 22uF; C_1206_3216Metric; LCSC Part # C12891
D1: SS34; D_SMA; LCSC Part # C8678
D2: green; LED_0805_2012Metric; LCSC Part # C2297
J1: PMOD; PinHeader_2x06_P2.54mm_Horizontal; JLCPCB Position Offset -6.35,-1.5
J2, J3: Conn_01x09_Pin; PinHeader_1x09_P2.54mm_Vertical; LCSC Part # C2932701
J4: Conn_01x03_Pin; PinHeader_1x03_P2.54mm_Vertical; LCSC Part # C2932698
L1: 4.7uH; L_6.3x6.3_H3; LCSC Part # C142106
R1: 220k; R_0805_2012Metric; LCSC Part # C17556
R2: 30k; R_0805_2012Metric; LCSC Part # C17621
R3: 1k2; R_0805_2012Metric; LCSC Part # C17379
TP1, TP2: TestPoint; TestPoint_Pad_D1.5mm
U1: EA2208; SOT-23-6; LCSC Part # C22462489
U2: Waveshare RP2024 ZERO; Waveshare-RP2040-ZERO; not fitted

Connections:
3.3V: C1.1, J1.1, J1.2, L1.1, U1.4 (RUN), U1.5 (PWR)
5V: C2.1, D1.1 (K), J2.1, R1.1, R3.1
/A10: J1.12, J3.5
/A11: J1.11, J3.8
/CSn: J1.10, J3.6
/GP3: J1.7
/GP14: J2.9
/IO13: J1.9, J3.7
/IRQn: J1.8, J3.9
/K5: J1.6, TP2.1
/L5: J1.5, TP1.1
/UART_RX: J3.2, J4.3
/UART_TX: J3.1, J4.2
GND: C1.2, C2.2, D2.1 (K), J1.3, J1.4, J2.2, J4.1, R2.2, U1.2 (GND)
unnamed: D1.2 (A), L1.2, U1.1 (SWITCH)
unnamed: D2.2 (A), R3.2
unnamed: R1.2, R2.1, U1.3 (FBK)

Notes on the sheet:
5V Boost Converter

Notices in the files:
board/misteryshield20k_rpipico/MiSTeryShield20kRPiPicoUSB.kicad_pcb:
(c) 2025 by Stefan Voss
